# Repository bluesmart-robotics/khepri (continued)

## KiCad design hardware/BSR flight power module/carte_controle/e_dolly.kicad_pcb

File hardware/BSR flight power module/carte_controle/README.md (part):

# Carte de contrôle — BSR flight power module (KHEPRI)

Carte « cerveau » de l'instrument de tableau de bord KHEPRI (motorisation,
IHM, variomètre, alimentation de secours). Elle est empilée sur la
**BSR Drive 3.7**, la carte de puissance qui pilote les deux moteurs.

Projet KiCad 9 (`e_dolly.kicad_pro`, nom hérité de la carte E-dolly dont elle
dérive), 4 couches, **80 × 150 mm**.

> Cette copie a volontairement divergé de la carte de contrôle du dépôt
> E-dolly, qui garde son E-stop et ses contacteurs. Ne pas reporter les
> changements dans E-dolly.

---

## 1. Vue d'ensemble

```
                XT60 2+4 J17 vers la BSR Drive (bus pack 42-51 V)
                                   │
          ┌────────────────────────┴───────────────────────────┐
          │  TVS U8 ─ U2 TPS54560 ─► +24V ─┬─► ventilateur J25  │
          │                                ├─► chargeur secours │
          │                                └─► diode idéale ─┐  │
          │   cellules 2S J21+J22 ─► Q14 ─► diode idéale ────┤  │
          │                                       VSYS_OR ─ R70 ─► +VSYS
          │      +VSYS ─┬─► U1 MP2565 ─► +3.3V (ESP32, logique) │
          │             ├─► U20 L78L05 ─► +5V_SENS ─► 3 LDO capteurs
          │             └─► U30 AP63205 ─► +5V_IHM ─► façade (J20)
          │                                                     │
          │  +36V ─ U43 LM5146 ─► +24V_EXT 10 A ─► J26 faisceau     │
          │  ESP32 U6 ── CAN (U3) ── J28 (BSR Drive) / J26 (faisceau)
          │      ├── I²C ─ TCA9548A U5 ─ ch0 PMP / ch1 secours /  │
          │      │            ch2 pression / ch3 env. / ch4 PCA9555│
          │      ├── SPI ─ IMU U4                                  │
          │      ├── UART1/UART2 ─ façade (J20)                    │
          │      └── PWM/tachy ─ ventilateur (J25)                 │
          └─────────────────────────────────────────────────────┘
```

L'ESP32 de cette carte est la **référence unique** : il est le seul à envoyer
les consignes à la BSR Drive (CAN). La façade (smart knob, écrans) ne fait que
proposer des consignes, que l'ESP32 valide.

### Feuilles du schéma

| Feuille | Contenu |
|---|---|
| `e_dolly.kicad_sch` (racine) | ESP32, CAN, IMU, multiplexeur I²C, USB, alimentations 24 V et 3,3 V, mesure de tension bus |
| `capteurs_pression.kicad_sch` | variomètre et anémomètre : 2 × MS5611 + HSC, leurs alimentations |
| `liaison_ihm.kicad_sch` | nappe vers la carte façade, alimentation 5V_IHM |
| `alim_secours.kicad_sch` | batterie de secours 2S, chargeur, jauge, OU par diodes idéales |
| `mesures_env.kicad_sch` | température d'air, courant et tension consommés par l'instrument |
| `interface_pmp.kicad_sch` | liaison vers la carte de charge USB-C EPR (PMP41115) |
| `ventilation.kicad_sch` | commande du ventilateur de la BSR Drive |
| `faisceau_au.kicad_sch` | XT60 J17, trous de fixation, liaison BSR Drive, faisceau chaussettes 24 V, arrêt d'urgence, expandeur I²C |

---

## 2. Alimentations

| Rail | Produit par | Depuis | Alimente |
|---|---|---|---|
| **+36V** (nom historique) | — | bus du pack 42–51 V via la XT60 J17 | U2, U43, mesure bus (R41–R43), TVS U8 SMCJ58A, C24 100 µF |
| **+24V_EXT** (≈ 24,3 V, 10 A) | U43 LM5146 + Q18/Q19 NTMFS6H800NL, L16 10 µH XAL1510 | +36V | faisceau des chaussettes (J26), coupable |
| **+24V** (≈ 25 V) | U2 TPS54560, L2 15,4 µH, D2 | +36V | diode idéale bus (U36/Q12), 5V_CHG (U34), ventilateur J25 |
| **VSYS_OR** | OU de U36/Q12 (bus) et U37/Q13 (secours) | +24V ou cellules 2S | shunt R70 |
| **+VSYS** | R70 20 mΩ | VSYS_OR | U1, U20, U30. Vaut ≈ 25 V sur bus, 6–8,4 V sur secours |
| **+3.3V** | U1 MP2565, L1 10 µH | +VSYS | ESP32, CAN, IMU, TCA9548A, CP2102N, I²C |
| **+5V_SENS** | U20 L78L05 (100 mA) | +VSYS | 3 LDO LP5907 des capteurs de pression |
| **+3V3_STAT / _TE / _PITOT** | U21 / U22 / U23 LP5907, ferrites L10–L12 | +5V_SENS | un capteur de pression chacun |
| **+5V_IHM** (2 A) | U30 AP63205, L13 6,8 µH | +VSYS | carte façade (J20), coupable par IO13 |
| **+5V_CHG** | U34 AP63205, L14 6,8 µH | +24V (bus seul) | chargeur BQ25887 |
| **BAT_P** (6–8,4 V) | cellules 2S J21 + J22 via F1 | — | chargeur, jauge, Q14 |

Points à comprendre :
- **Sans bus** (planeur éteint, BMS ouvert), +24V tombe. Si l'interrupteur
  J23 est fermé, la batterie de secours alimente +VSYS via U37/Q13 :
  l'instrument démarre, affiche, logue et peut envoyer l'ordre CAN d'armement
  au BMS. Quand le bus arrive, +24V (25 V) dépasse la batterie (≤ 8,4 V) et
  la diode idéale côté secours se bloque toute seule.
- **Tout ce qui est en aval de +VSYS doit accepter 6 V** : U1 (VIN ≥ 4,5 V),
  U30 (VIN ≥ 3,8 V, sortie 5 V un peu juste à 6 V), U20 L78L05 (sortie ≈ 4,3 V
  à 6 V d'entrée, suffisant pour les LDO 3,3 V).
- Le chargeur n'est alimenté que par le bus (U34 sur +24V) : il ne peut pas
  « se charger lui-même » en boucle sur la batterie.

Valeurs à recontrôler : U2 sortie = 0,8 V × (1 + R21/R22) = 0,8 × (1 + 100k/3,3k)
≈ 25 V ; U1 sortie = 0,8 V × (1 + R18/R14) = 0,8 × (1 + 127k/40,2k) ≈ 3,33 V.

---

## 3. Calculateur et communications

### ESP32-WROOM-32UE (U6) — affectation de toutes les broches

| GPIO | Broche | Fonction | Réseau | Vers |
|---|---|---|---|---|
| EN | 3 | reset | /EN | SW1, R25/C17 |
| IO0 | 25 | boot | /IO0 | SW2, R27 |
| IO1 / IO3 | 35 / 34 | UART0 programmation et console | ESP_TX / ESP_RX | CP2102N U7, LED D4/D3 |
| IO16 / IO17 | 27 / 28 | CAN RX / TX | /RXD, /TXD | SN65HVD230 U3 |
| IO5 / IO4 | 29 / 26 | I²C principal SDA / SCL (pull-up R23/R20) | /SDA, /SCL | TCA9548A U5 |
| IO22 / IO23 / IO25 | 36 / 37 / 10 | SPI SCLK / MOSI / MISO | /SCLK /MOSI /MISO | IMU U4 |
| IO26 | 11 | SPI CS IMU (pull-up R17) | /IO26 | U4 |
| IO27 | 12 | interruption IMU | /IO27 | U4 INT1 |
| IO33 | 9 | ADC tension bus | /PDT_pwr_switched | pont R41+R42 / R43, R44, C25, clamp D7 |
| IO18 / IO34 | 30 / 6 | UART1 TX / RX ↔ STM32 haptique | IHM_TX1 / IHM_RX1 | J20 |
| IO19 / IO35 | 31 / 7 | UART2 TX / RX ↔ ESP32-S3 façade | IHM_TX2 / IHM_RX2 | J20 |
| IO21 | 33 | NRST du STM32 (drain ouvert) | IHM_NRST | J20 |
| IO14 | 13 | BOOT0 du STM32 | IHM_BOOT0 | J20 |
| IO13 | 16 | coupure 5V_IHM (haut = coupé) | IHM_PWR_OFF | Q10 |
| IO36 (SENSOR_VP) | 4 | interruption commune (entrée seule) | INT_PWR | PMP, BQ25887, MAX17205, TMP117, INA226 |
| IO12 | 14 | autorisation de charge PMP (pull-down R84, **doit rester bas au boot**) | PMP_CHG_EN | J24 |
| IO15 | 23 | PWM ventilateur | FAN_PWM | Q15 |
| IO39 (SENSOR_VN) | 5 | tachymètre ventilateur (entrée seule) | FAN_TACH | J25 |

**Plus aucune broche libre.** Les commandes ajoutées ensuite (faisceau,
arrêt d'urgence) passent par l'expandeur PCA9555 (§ 9).

### CAN — U3 SN65HVD230

- Relié à la BSR Drive par J28 et au faisceau des chaussettes par J26 (§ 9).
  L'ancienne XT60 J17 et l'ancien connecteur J4 sont supprimés.
- Terminaison 120 Ω (R112) **commutable** par le cavalier JP1 « TERM CAN ».
  L'ancienne terminaison fixe R19 est supprimée.
- R15 10 k sur Rs : mode pente contrôlée.

### I²C — multiplexeur TCA9548A (U5, 0x70)

| Canal | Réseau | Composants (adresse) | Pull-up |
|---|---|---|---|
| 0 | I2C_PMP | carte de charge PMP41115 via J24 | R82/R83 4,7 k |
| 1 | I2C_PWR | BQ25887 (0x6B), MAX17205 (0x36 et 0x0B) | R99/R100 4,7 k |
| 2 | I2C_PRES | MS5611 statique (0x76), MS5611 TE (0x77), HSC (0x28) | R50/R51 4,7 k (sur +3V3_STAT) |
| 3 | I2C_ENV | TMP117 (0x48), INA226 (0x40) | R80/R81 4,7 k |
| 4 | I2C_X | PCA9555 (0x20) | R107/R108 4,7 k |
| 5–7 | — | libres | — |

### Autres

- **IMU U4 ICM-42688-P** (accéléromètre et gyroscope 6 axes, SPI) : fusion
  avec les capteurs de pression pour le vario.
- **USB U7 CP2102N** : programmation de l'ESP32 par J14 (JST PH 6 vers une
  prise USB-C déportée), LED TX/RX D3/D4, reset automatique.
- **SW1** = EN (reset), **SW2** = IO0 (boot).

---

## 4. Variomètre et anémomètre (`capteurs_pression.kicad_sch`, haut de carte)

| Capteur | Réf. | Mesure | Repère sérigraphie |
|---|---|---|---|
| MS5611 | U24 | pression statique (altitude, vario brut) | `P-statique` |
| MS5611 | U25 | pression de la sonde d'énergie totale (vario compensé) | `P-TE` |
| HSCMRRN001PD2A3 | U26 | Δp pitot ±1 psi (vitesse air) | `Δp pitot`, ports `P-tot` / `P-stat` |

- Chaque capteur a sa propre chaîne d'alimentation : ferrite, LDO LP5907
  3,3 V faible bruit et découplage, pour que le bruit numérique ne pollue pas
  la mesure.
- Les deux MS5611 sont chacun dans une **zone de capot étanche** de
  11 × 12 mm (`CAPOT_STATIQUE`, `CAPOT_TE`) : contour en sérigraphie et zone
  d'interdiction de vias, car un via sous le capot ferait fuir l'air. Les capots
  sont imprimés en 3D et reliés aux prises par tube.
- Le HSC a ses propres embouts cannelés ; ses ports sortent vers le bord haut.

---

## 5. Liaison façade (`liaison_ihm.kicad_sch`, bord droit)

Une seule nappe **J20 JST-GH 12 voies** vers la carte façade (smart knob
STM32 + écran 1,64" ESP32-S3 fusionnés ; l'écran 1,75" est raccordé à la
façade). Tout est en 3,3 V.

| J20 | Signal | ESP32 |
|---|---|---|
| 1, 2, 3 | +5V_IHM (2 A au total) | — |
| 4, 11, 12 | GND | — |
| 5 | TX1 → RX du STM32 | IO18 |
| 6 | RX1 ← TX du STM32 | IO34 |
| 7 | TX2 → RX de l'ESP32-S3 | IO19 |
| 8 | RX2 ← TX de l'ESP32-S3 | IO35 |
| 9 | NRST du STM32 | IO21 |
| 10 | BOOT0 du STM32 | IO14 |

- **Côté façade, croiser TX et RX.** Prendre l'USART1 du STM32 (PA9/PA10)
  pour que le reflash par BOOT0 fonctionne.
- Protections : 100 Ω en série sur chaque ligne (R54–R59), pull-up 10 k sur
  les deux RX (R60/R61, IO34/35 n'en ont pas), pull-down 10 k sur BOOT0
  (R62), diodes ESD TPD4E05U06 (U31, U32).
- Alimentation : U30 AP63205. Son EN est tiré à +VSYS (R52) ; Q10 le met à la
  masse quand IO13 est haut. La façade est donc alimentée par défaut, et
  l'ESP32 peut la redémarrer à froid.

---

## 6. Alimentation de secours (`alim_secours.kicad_sch`, bande gauche)

- **Deux cellules Li-ion 18650 en série (2S)**. J21 à gauche = cellule basse,
  J22 à droite = cellule haute, JST PH 2.0 2 voies, **1 = −, 2 = +** sur les
  deux. Le point milieu BAT_MID relie le + de J21 au − de J22.
  **Cellules protégées (PCM intégré) obligatoires.**
  Pourquoi la série : à 6–8,4 V, la batterie se met en OU directement sur
  +VSYS, sans convertisseur élévateur.
- **F1** fusible réarmable 1812 sur le + de la pile, **R71** 10 mΩ côté −
  (shunt de la jauge).
- **J23 interrupteur de tableau de bord** (PH 2.0 2P) : contact fermé entre
  les broches 1 et 2 → Q14 (PMOS AO3401A) conduit et branche la batterie.
  Ouvert, la batterie est isolée : elle ne se vide pas au parking. Une diode
  idéale seule ne suffirait pas, la diode interne du MOSFET conduirait.
- **OU par diodes idéales** : U36 LM74700 + Q12 SI2318 côté bus (+24V),
  U37 + Q13 côté secours (BAT_SW). Sortie commune VSYS_OR → R70 → +VSYS.
- **Chargeur U35 BQ25887** (élévateur 2S, équilibrage des cellules, I²C 0x6B) :
  - entrée +5V_CHG (U34, depuis le bus seulement) ;
  - courant d'entrée limité à 1 A max par R88 1,27 kΩ, réglable plus bas en I²C ;
  - équilibrage par R91 100 Ω (≈ 40 mA), R92 300 Ω de protection sur MID ;
  - thermistance TH1 (pont R89/R90) ;
  - CD et PSEL à la masse (charge autorisée, mode adaptateur) ;
  - ~INT sur INT_PWR ; ~PG et ~STAT non utilisés.
- **Jauge U38 MAX17205** (ModelGauge m5) : état de charge, tension de chaque
  cellule, courant via R71 ; I²C 0x36 / 0x0B ; alerte sur INT_PWR ;
  thermistance TH2 sur AIN1.

---

## 7. Mesures d'environnement et carte de charge

**`mesures_env.kicad_sch`** (en haut à gauche, à côté des capteurs de
pression) :
- **U40 TMP117** (0x48, ±0,1 °C) : température de l'air, pour la vitesse
  vraie et la densité. À garder loin des sources de chaleur.
- **U41 INA226** (0x40) : courant et tension de +VSYS, c'est-à-dire la
  consommation totale de l'instrument, sur bus comme sur secours. Shunt R70
  20 mΩ, filtre R96/R97/C62.

**`interface_pmp.kicad_sch`** — J24 JST PH 2.0 6 voies, sérigraphie
« to USB-C EPR », vers la carte de charge PMP41115 empilée :

| J24 | Signal |
|---|---|
| 1 | GND |
| 2 | +3,3 V (référence logique et pull-up) |
| 3 / 4 | SDA / SCL (canal 0) |
| 5 | INT (ligne commune INT_PWR, drain ouvert, pull-up R85) |
| 6 | CHG_EN (IO12, pull-down R84) |

La puissance de charge (240 W) ne passe pas par ce connecteur : elle va directement
sur le bus du pack.

---

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
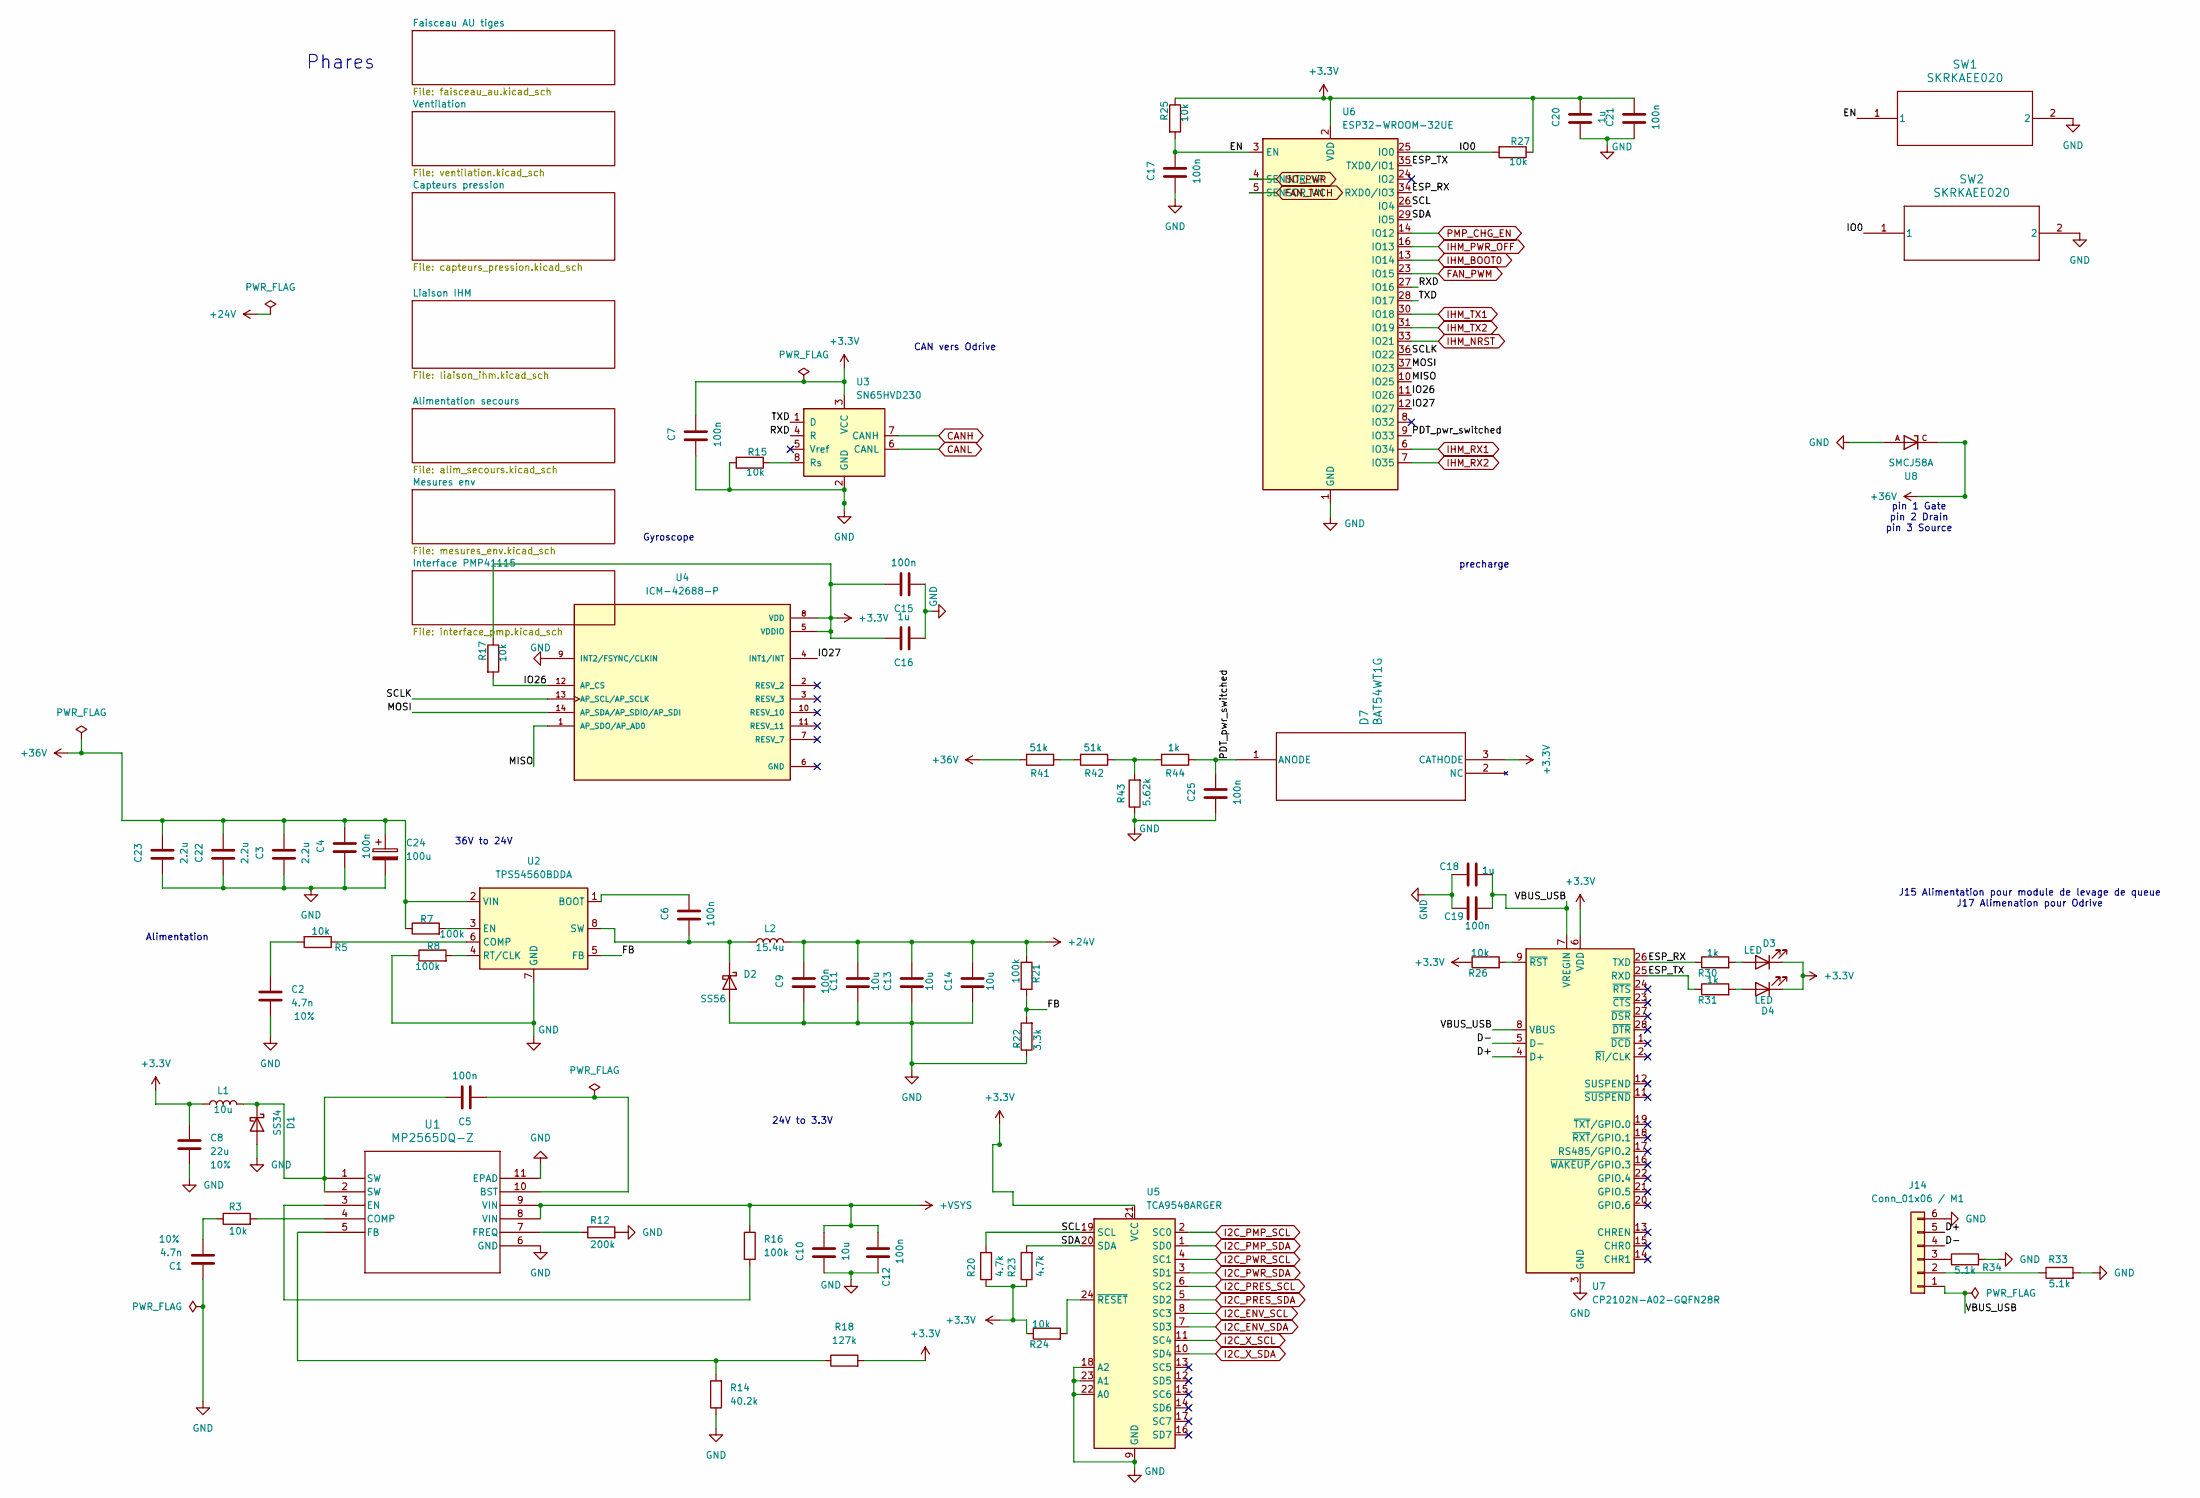
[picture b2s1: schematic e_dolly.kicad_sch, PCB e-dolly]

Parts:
C1, C2: 4.7n; C_0603_1608Metric; tolerance 10%; MPN CL10B472KB8NNNC; LCSC C1621
C3, C22, C23: 2.2u; C_1210_3225Metric; MPN GRM32ER72A225KA35L; LCSC C86054
C4: 100n; C_0805_2012Metric; MPN GCM21BR72A104KA37L; LCSC C85866
C5, C6, C7, C9, C12, C15, C17, C19, C21, C25: 100n; C_0603_1608Metric; MPN CL10B104KB8NNNC; LCSC C1591
C8: 22u; C_1206_3216Metric; tolerance 10%; MPN CL31A226KQHNNNE; LCSC C159759
C10: 10u; C_0805_2012Metric; MPN CL21A106KOQNNNE; LCSC C1713
C11, C13, C14: 10u; C_1210_3225Metric; MPN GRM32ER71H106KA12L; LCSC C77102
C16, C18, C20: 1u; C_0603_1608Metric; MPN CL10A105KB8NNNC; LCSC C15849
C24: 100u; CP_Elec_10x10.5; MPN EEEFN1J101P; LCSC C494866
D1: SS34; D_SMB; MPN DSS34; LCSC C41369490
D2: SS56; D_SMA; MPN SS56; LCSC C65009
D3, D4: LED; D_SOD-323; MPN LTST-C235KGKRKT; LCSC C125110
D7: BAT54WT1G; SOT-323-3_2P2X1P35_ONS
J14: Conn_01x06 / M1; JST_PH_B6B-PH-K_1x06_P2.00mm_Vertical; MPN B6B-PH-K-S(LF)(SN); LCSC C131342
L1: 10u; L_7.1x6.6mm; MPN SMMS0650-100M; LCSC C149584
L2: 15.4u; L_7.1x6.6mm; MPN SMMS0650-150M; LCSC C149585
R3: 10k; R_0603_1608Metric; MPN RT0603BRD0710KL; LCSC C95204
R5, R15, R17, R24, R25, R26, R27: 10k; R_0402_1005Metric; MPN RC0402FR-0710KL; LCSC C60490
R7, R8, R16, R21: 100k; R_0603_1608Metric; MPN RC0603FR-07100KL; LCSC C14675
R12: 200k; R_0603_1608Metric; MPN RC0603FR-07200KL; LCSC C105574
R14: 40.2k; R_0603_1608Metric; MPN RC0603FR-0740K2L; LCSC C137723
R18: 127k; R_0603_1608Metric; MPN RT0603FRE07127KL; LCSC C706120
R20, R23: 4.7k; R_0603_1608Metric; MPN RC0603FR-074K7L; LCSC C99782
R22: 3.3k; R_0402_1005Metric; MPN RC0603FR-073K3L; LCSC C108078
R30, R31, R44: 1k; R_0603_1608Metric; MPN RC0603FR-071KL; LCSC C22548
R33, R34: 5.1k; R_0603_1608Metric; MPN RC0603FR-075K1L; LCSC C105580
R41, R42: 51k; R_0805_2012Metric; MPN RC0805FR-0751KL; LCSC C107233
R43: 5.62k; R_0603_1608Metric; MPN RC0603FR-075K62L; LCSC C183220
SW1, SW2: SKRKAEE020; SW2_SKRKAEE020_ALPS; MPN SKRKAEE020; LCSC C115357
U1: MP2565DQ-Z; QFN10_MP2565_MNP; MPN MP2459GJ-Z-MS; LCSC C45367195
U2: TPS54560BDDA; Texas_R-PDSO-G8_EP2.95x4.9mm_Mask2.4x3.1mm_ThermalVias; MPN TPS54560DDA; LCSC C465738
U3: SN65HVD230; SOIC-8_3.9x4.9mm_P1.27mm; MPN SN65HVD230DR-JSM; LCSC C46596299
U4: ICM-42688-P; PQFN50P300X250X97-14N; PARTREV 1.2; LCSC C1850418
U5: TCA9548ARGER; Texas_RGE0024C_VQFN-24-1EP_4x4mm_P0.5mm_EP2.1x2.1mm; MPN TCA9548ARGER; LCSC C555456
U6: ESP32-WROOM-32UE; MPN ESP32-WROOM-32UE-N16; LCSC C701346
U7: CP2102N-A02-GQFN28R; QFN-28-1EP_5x5mm_P0.5mm_EP3.35x3.35mm; MPN CP2102N-A02-GQFN28R; LCSC C964632
U8: SMCJ58A; DIOM6859X262N; PARTREV R2102; LCSC C3720689

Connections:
+3.3V: C7.2, C8.1, C15.2, C16.2, C20.2, C21.2, D3.1 (K), D4.1 (K), D7.3 (CATHODE), L1.1, R17.1, R18.2, R20.1, R23.1, R24.1, R25.1, R26.1, R27.1, U3.3 (VCC), U4.5 (VDDIO), U4.8 (VDD), U5.21 (VCC), U6.2 (VDD), U7.6 (VDD); also elsewhere on the board
+24V: C9.2, C11.2, C13.2, C14.2, L2.2, R21.1; also elsewhere on the board
+36V: C3.2, C4.2, C22.2, C23.2, C24.1, R7.1, R41.2, U2.2 (VIN), U8.C; also elsewhere on the board
+VSYS: C10.2, C12.2, R16.1, U1.8 (VIN), U1.9 (VIN); also elsewhere on the board
/D+: J14.5, U7.4 (D+)
/D-: J14.4, U7.5 (D-)
/EN: C17.2, R25.2, SW1.1, U6.3 (EN)
/ESP_RX: R30.1, U6.34 (RXD0/IO3), U7.26 (TXD)
/ESP_TX: R31.1, U6.35 (TXD0/IO1), U7.25 (RXD)
/FB: R21.2, R22.2, U2.5 (FB)
/IO0: R27.2, SW2.1, U6.25 (IO0)
/IO26: R17.2, U4.12 (AP_CS), U6.11 (IO26)
/IO27: U4.4 (INT1/INT), U6.12 (IO27)
/MISO: U4.1 (AP_SDO/AP_AD0), U6.10 (IO25)
/MOSI: U4.14 (AP_SDA/AP_SDIO/AP_SDI), U6.37 (IO23)
/PDT_pwr_switched: C25.2, D7.1 (ANODE), R44.1, U6.9 (IO33)
/RXD: U3.4 (R), U6.27 (IO16)
/SCL: R20.2, U5.19 (SCL), U6.26 (IO4)
/SCLK: U4.13 (AP_SCL/AP_SCLK), U6.36 (IO22)
/SDA: R23.2, U5.20 (SDA), U6.29 (IO5)
/TXD: U3.1 (D), U6.28 (IO17)
/VBUS_USB: C18.2, C19.2, J14.1, U7.7 (VREGIN), U7.8 (VBUS)
CANH: U3.7 (CANH); also elsewhere on the board
CANL: U3.6 (CANL); also elsewhere on the board
FAN_PWM: U6.23 (IO15); also elsewhere on the board
FAN_TACH: U6.5 (SENSOR_VN); also elsewhere on the board
GND: C1.1, C2.2, C3.1, C4.1, C7.1, C8.2, C9.1, C10.1, C11.1, C12.1, C13.1, C14.1, C15.1, C16.1, C17.1, C18.1, C19.1, C20.1, C21.1, C22.1, C23.1, C24.2, C25.1, D1.2 (A), D2.2 (A), J14.6, R8.1, R12.2, R14.1, R15.2, R22.1, R33.2, R34.2, R43.1, SW1.2, SW2.2, U1.6 (GND), U1.11 (EPAD), U2.7 (GND), U2.9 (GND), U3.2 (GND), U4.9 (INT2/FSYNC/CLKIN), U5.9 (GND), U5.18 (A2), U5.22 (A0), U5.23 (A1), U6.1 (GND), U6.15 (GND), U6.38 (GND), U6.39 (GND), U7.3 (GND), U7.29 (GND), U8.A; also elsewhere on the board
I2C_ENV_SCL: U5.8 (SC3); also elsewhere on the board
I2C_ENV_SDA: U5.7 (SD3); also elsewhere on the board
I2C_PMP_SCL: U5.2 (SC0); also elsewhere on the board
I2C_PMP_SDA: U5.1 (SD0); also elsewhere on the board
I2C_PRES_SCL: U5.6 (SC2); also elsewhere on the board
I2C_PRES_SDA: U5.5 (SD2); also elsewhere on the board
I2C_PWR_SCL: U5.4 (SC1); also elsewhere on the board
I2C_PWR_SDA: U5.3 (SD1); also elsewhere on the board
I2C_X_SCL: U5.11 (SC4); also elsewhere on the board
I2C_X_SDA: U5.10 (SD4); also elsewhere on the board
IHM_BOOT0: U6.13 (IO14); also elsewhere on the board
IHM_NRST: U6.33 (IO21); also elsewhere on the board
IHM_PWR_OFF: U6.16 (IO13); also elsewhere on the board
IHM_RX1: U6.6 (IO34); also elsewhere on the board
IHM_RX2: U6.7 (IO35); also elsewhere on the board
IHM_TX1: U6.30 (IO18); also elsewhere on the board
IHM_TX2: U6.31 (IO19); also elsewhere on the board
INT_PWR: U6.4 (SENSOR_VP); also elsewhere on the board
unnamed: C1.2, R3.1
unnamed: C2.1, R5.2
unnamed: C5.2, D1.1 (K), L1.2, U1.1 (SW), U1.2 (SW)
unnamed: C6.1, D2.1 (K), L2.1, U2.8 (SW)
unnamed: D3.2 (A), R30.2
unnamed: D4.2 (A), R31.2
unnamed: J14.2, R33.1
unnamed: J14.3, R34.1
unnamed: R41.1, R42.2
unnamed: R42.1, R43.2, R44.2
unnamed: C5.1, U1.10 (BST)
unnamed: R3.2, U1.4 (COMP)
unnamed: R16.2, U1.3 (EN)
unnamed: R14.2, R18.1, U1.5 (FB)
unnamed: R12.1, U1.7 (FREQ)
unnamed: C6.2, U2.1 (BOOT)
unnamed: R5.1, U2.6 (COMP)
unnamed: R7.2, U2.3 (EN)
unnamed: R8.2, U2.4 (RT/CLK)
unnamed: R15.1, U3.8 (Rs)
unnamed: R24.2, U5.24 (~RESET)
unnamed: R26.2, U7.9 (~RST)
PMP_CHG_EN: U6.14 (IO12); also elsewhere on the board

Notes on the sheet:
Alimentation
pin 1 Gate pin 2 Drain pin 3 Source
Phares
36V to 24V
Gyroscope
precharge
24V to 3.3V
J15 Alimentation pour module de levage de queue J17 Alimenation pour Odrive
CAN vers Odrive

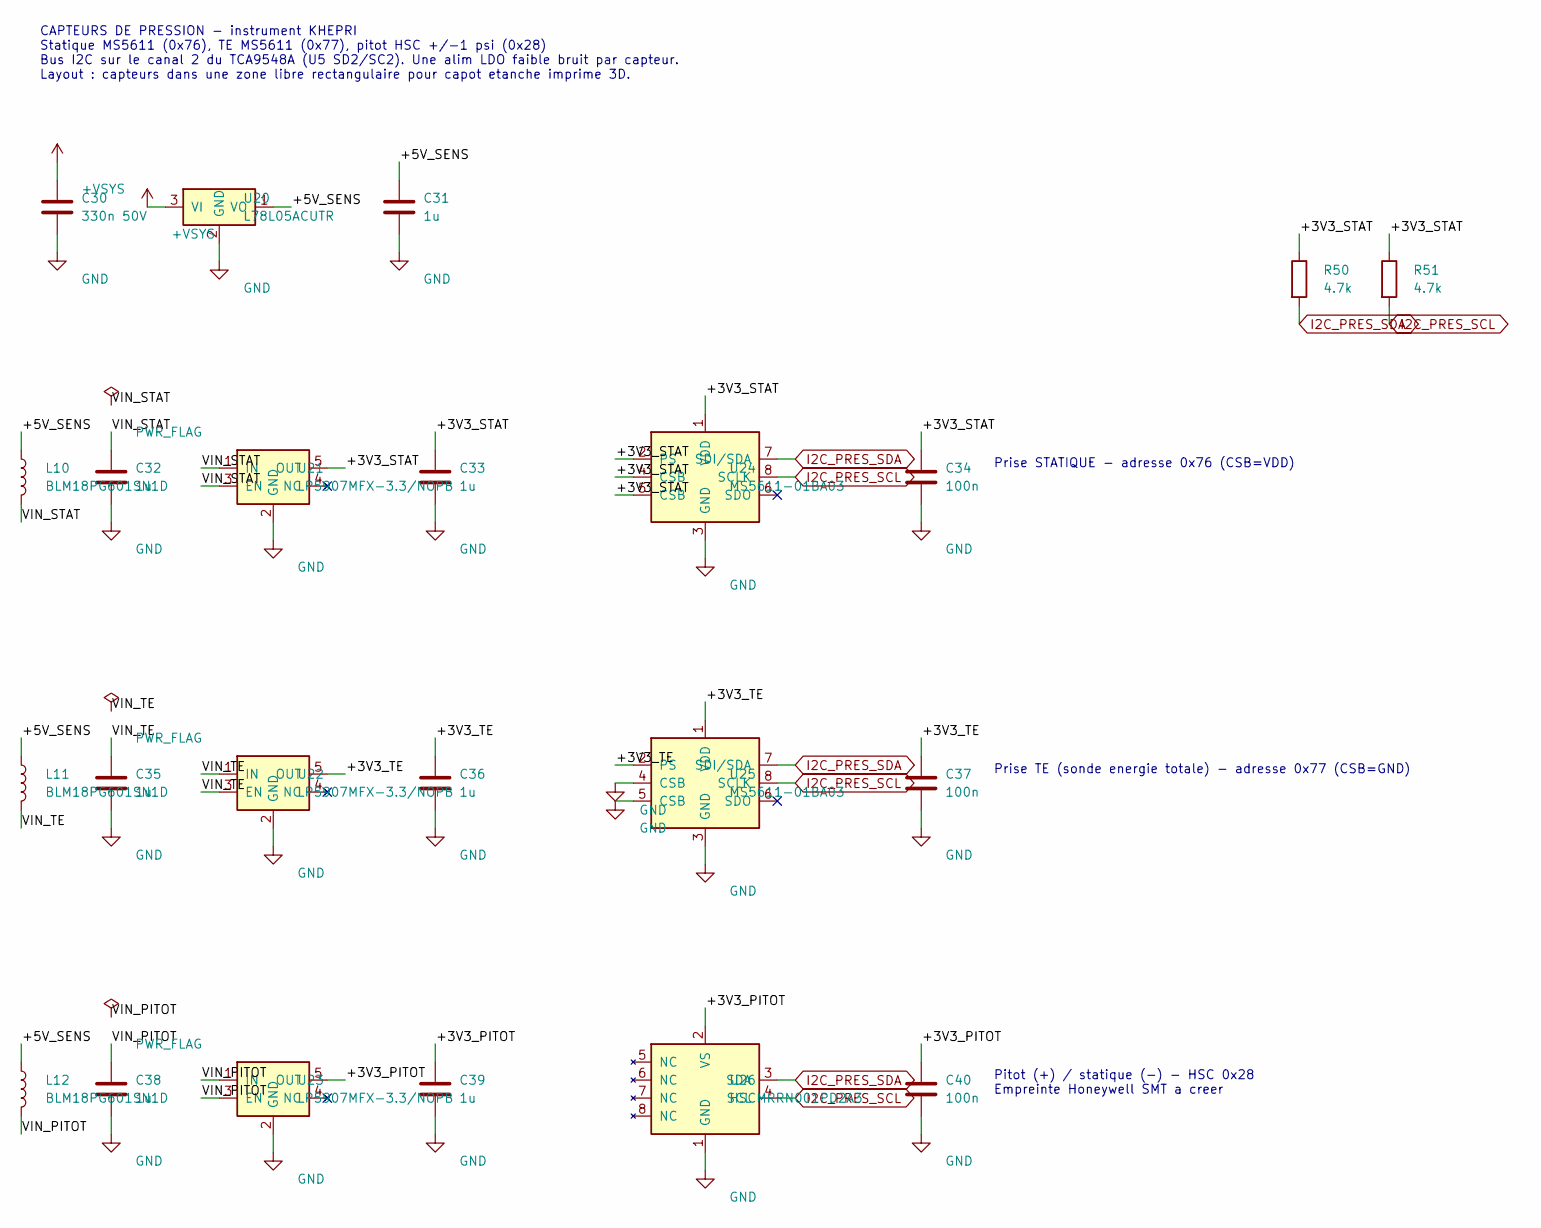
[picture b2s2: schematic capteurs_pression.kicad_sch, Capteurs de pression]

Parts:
C30: 330n 50V; C_0603_1608Metric
C31, C32, C33, C35, C36, C38, C39: 1u; C_0603_1608Metric
C34, C37, C40: 100n; C_0603_1608Metric
L10, L11, L12: BLM18PG601SN1D; L_0603_1608Metric
R50, R51: 4.7k; R_0603_1608Metric
U20: L78L05ACUTR; SOT-89-3
U21, U22, U23: LP5907MFX-3.3/NOPB; SOT-23-5
U24, U25: MS5611-01BA03; LGA-8_3x5mm_P1.25mm
U26: HSCMRRN001PD2A3; Honeywell_HSC_SMT_RR_PROVISOIRE

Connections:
+VSYS: C30.1, U20.3 (VI); also elsewhere on the board
/Capteurs pression/+3V3_PITOT: C39.1, C40.1, U23.5 (OUT), U26.2 (VS)
/Capteurs pression/+3V3_STAT: C33.1, C34.1, R50.1, R51.1, U21.5 (OUT), U24.1 (VDD), U24.2 (PS), U24.4 (CSB), U24.5 (CSB)
/Capteurs pression/+3V3_TE: C36.1, C37.1, U22.5 (OUT), U25.1 (VDD), U25.2 (PS)
/Capteurs pression/+5V_SENS: C31.1, L10.1, L11.1, L12.1, U20.1 (VO)
/Capteurs pression/VIN_PITOT: C38.1, L12.2, U23.1 (IN), U23.3 (EN)
/Capteurs pression/VIN_STAT: C32.1, L10.2, U21.1 (IN), U21.3 (EN)
/Capteurs pression/VIN_TE: C35.1, L11.2, U22.1 (IN), U22.3 (EN)
GND: C30.2, C31.2, C32.2, C33.2, C34.2, C35.2, C36.2, C37.2, C38.2, C39.2, C40.2, U20.2 (GND), U21.2 (GND), U22.2 (GND), U23.2 (GND), U24.3 (GND), U25.3 (GND), U25.4 (CSB), U25.5 (CSB), U26.1 (GND); also elsewhere on the board
I2C_PRES_SCL: R51.2, U24.8 (SCLK), U25.8 (SCLK), U26.4 (SCL); also elsewhere on the board
I2C_PRES_SDA: R50.2, U24.7 (SDI/SDA), U25.7 (SDI/SDA), U26.3 (SDA); also elsewhere on the board

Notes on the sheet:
CAPTEURS DE PRESSION - instrument KHEPRI Statique MS5611 (0x76), TE MS5611 (0x77), pitot HSC +/-1 psi (0x28) Bus I2C sur le canal 2 du TCA9548A (U5 SD2/SC2). Une alim LDO faible bruit par capteur. Layout : capteurs dans une zone libre rectangulaire pour capot etanche imprime 3D.
Prise STATIQUE - adresse 0x76 (CSB=VDD)
Prise TE (sonde energie totale) - adresse 0x77 (CSB=GND)
Pitot (+) / statique (-) - HSC 0x28 Empreinte Honeywell SMT a creer

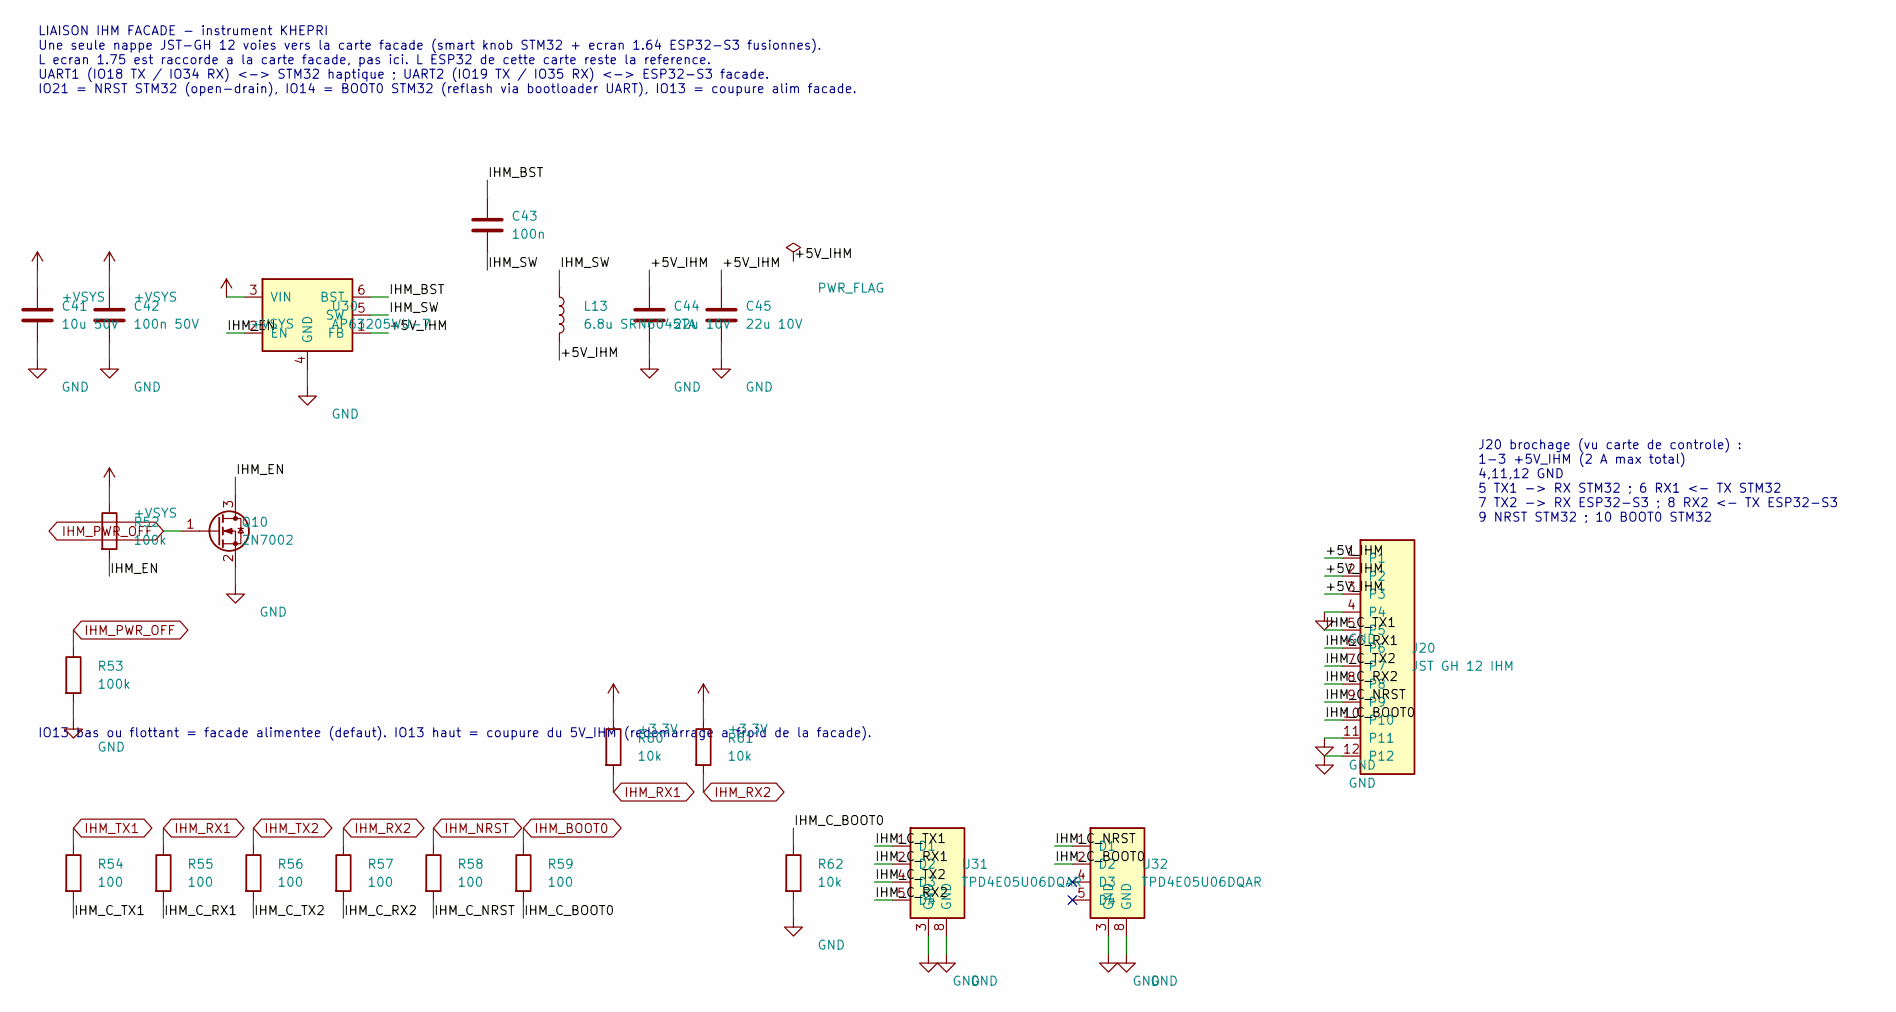
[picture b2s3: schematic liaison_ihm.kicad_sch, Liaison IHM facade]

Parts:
C41: 10u 50V; C_1206_3216Metric
C42: 100n 50V; C_0603_1608Metric
C43: 100n; C_0603_1608Metric
C44, C45: 22u 10V; C_0805_2012Metric
J20: JST GH 12 IHM; JST_GH_BM12B-GHS-TBT_1x12-1MP_P1.25mm_Vertical
L13: 6.8u SRN6045TA; L_Bourns_SRN6045TA
Q10: 2N7002; SOT-23
R52, R53: 100k; R_0603_1608Metric
R54, R55, R56, R57, R58, R59: 100; R_0603_1608Metric
R60, R61, R62: 10k; R_0603_1608Metric
U30: AP63205WU-7; TSOT-23-6
U31, U32: TPD4E05U06DQAR; USON-10_2.5x1.0mm_P0.5mm

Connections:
+3.3V: R60.1, R61.1; also elsewhere on the board
+VSYS: C41.1, C42.1, R52.1, U30.3 (VIN); also elsewhere on the board
/Liaison IHM/+5V_IHM: C44.1, C45.1, J20.1, J20.2, J20.3, L13.2, U30.1 (FB)
/Liaison IHM/IHM_BST: C43.1, U30.6 (BST)
/Liaison IHM/IHM_C_BOOT0: J20.10, R59.2, R62.1, U32.2 (D2)
/Liaison IHM/IHM_C_NRST: J20.9, R58.2, U32.1 (D1)
/Liaison IHM/IHM_C_RX1: J20.6, R55.2, U31.2 (D2)
/Liaison IHM/IHM_C_RX2: J20.8, R57.2, U31.5 (D4)
/Liaison IHM/IHM_C_TX1: J20.5, R54.2, U31.1 (D1)
/Liaison IHM/IHM_C_TX2: J20.7, R56.2, U31.4 (D3)
/Liaison IHM/IHM_EN: Q10.3 (D), R52.2, U30.2 (EN)
/Liaison IHM/IHM_SW: C43.2, L13.1, U30.5 (SW)
GND: C41.2, C42.2, C44.2, C45.2, J20.4, J20.11, J20.12, Q10.2 (S), R53.2, R62.2, U30.4 (GND), U31.3 (GND), U31.8 (GND), U32.3 (GND), U32.8 (GND); also elsewhere on the board
IHM_BOOT0: R59.1; also elsewhere on the board
IHM_NRST: R58.1; also elsewhere on the board
IHM_PWR_OFF: Q10.1 (G), R53.1; also elsewhere on the board
IHM_RX1: R55.1, R60.2; also elsewhere on the board
IHM_RX2: R57.1, R61.2; also elsewhere on the board
IHM_TX1: R54.1; also elsewhere on the board
IHM_TX2: R56.1; also elsewhere on the board

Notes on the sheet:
LIAISON IHM FACADE - instrument KHEPRI Une seule nappe JST-GH 12 voies vers la carte facade (smart knob STM32 + ecran 1.64 ESP32-S3 fusionnes). L ecran 1.75 est raccorde a la carte facade, pas ici. L ESP32 de cette carte reste la reference. UART1 (IO18 TX / IO34 RX) <-> STM32 haptique ; UART2 (IO19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
IO13 bas ou flottant = facade alimentee (defaut). IO13 haut = coupure du 5V_IHM (redemarrage a froid de la facade).
J20 brochage (vu carte de controle) : 1-3 +5V_IHM (2 A max total) 4,11,12 GND 5 TX1 -> RX STM32 ; 6 RX1 <- TX STM32 7 TX2 -> RX ESP32-S3 ; 8 RX2 <- TX ESP32-S3 9 NRST STM32 ; 10 BOOT0 STM32

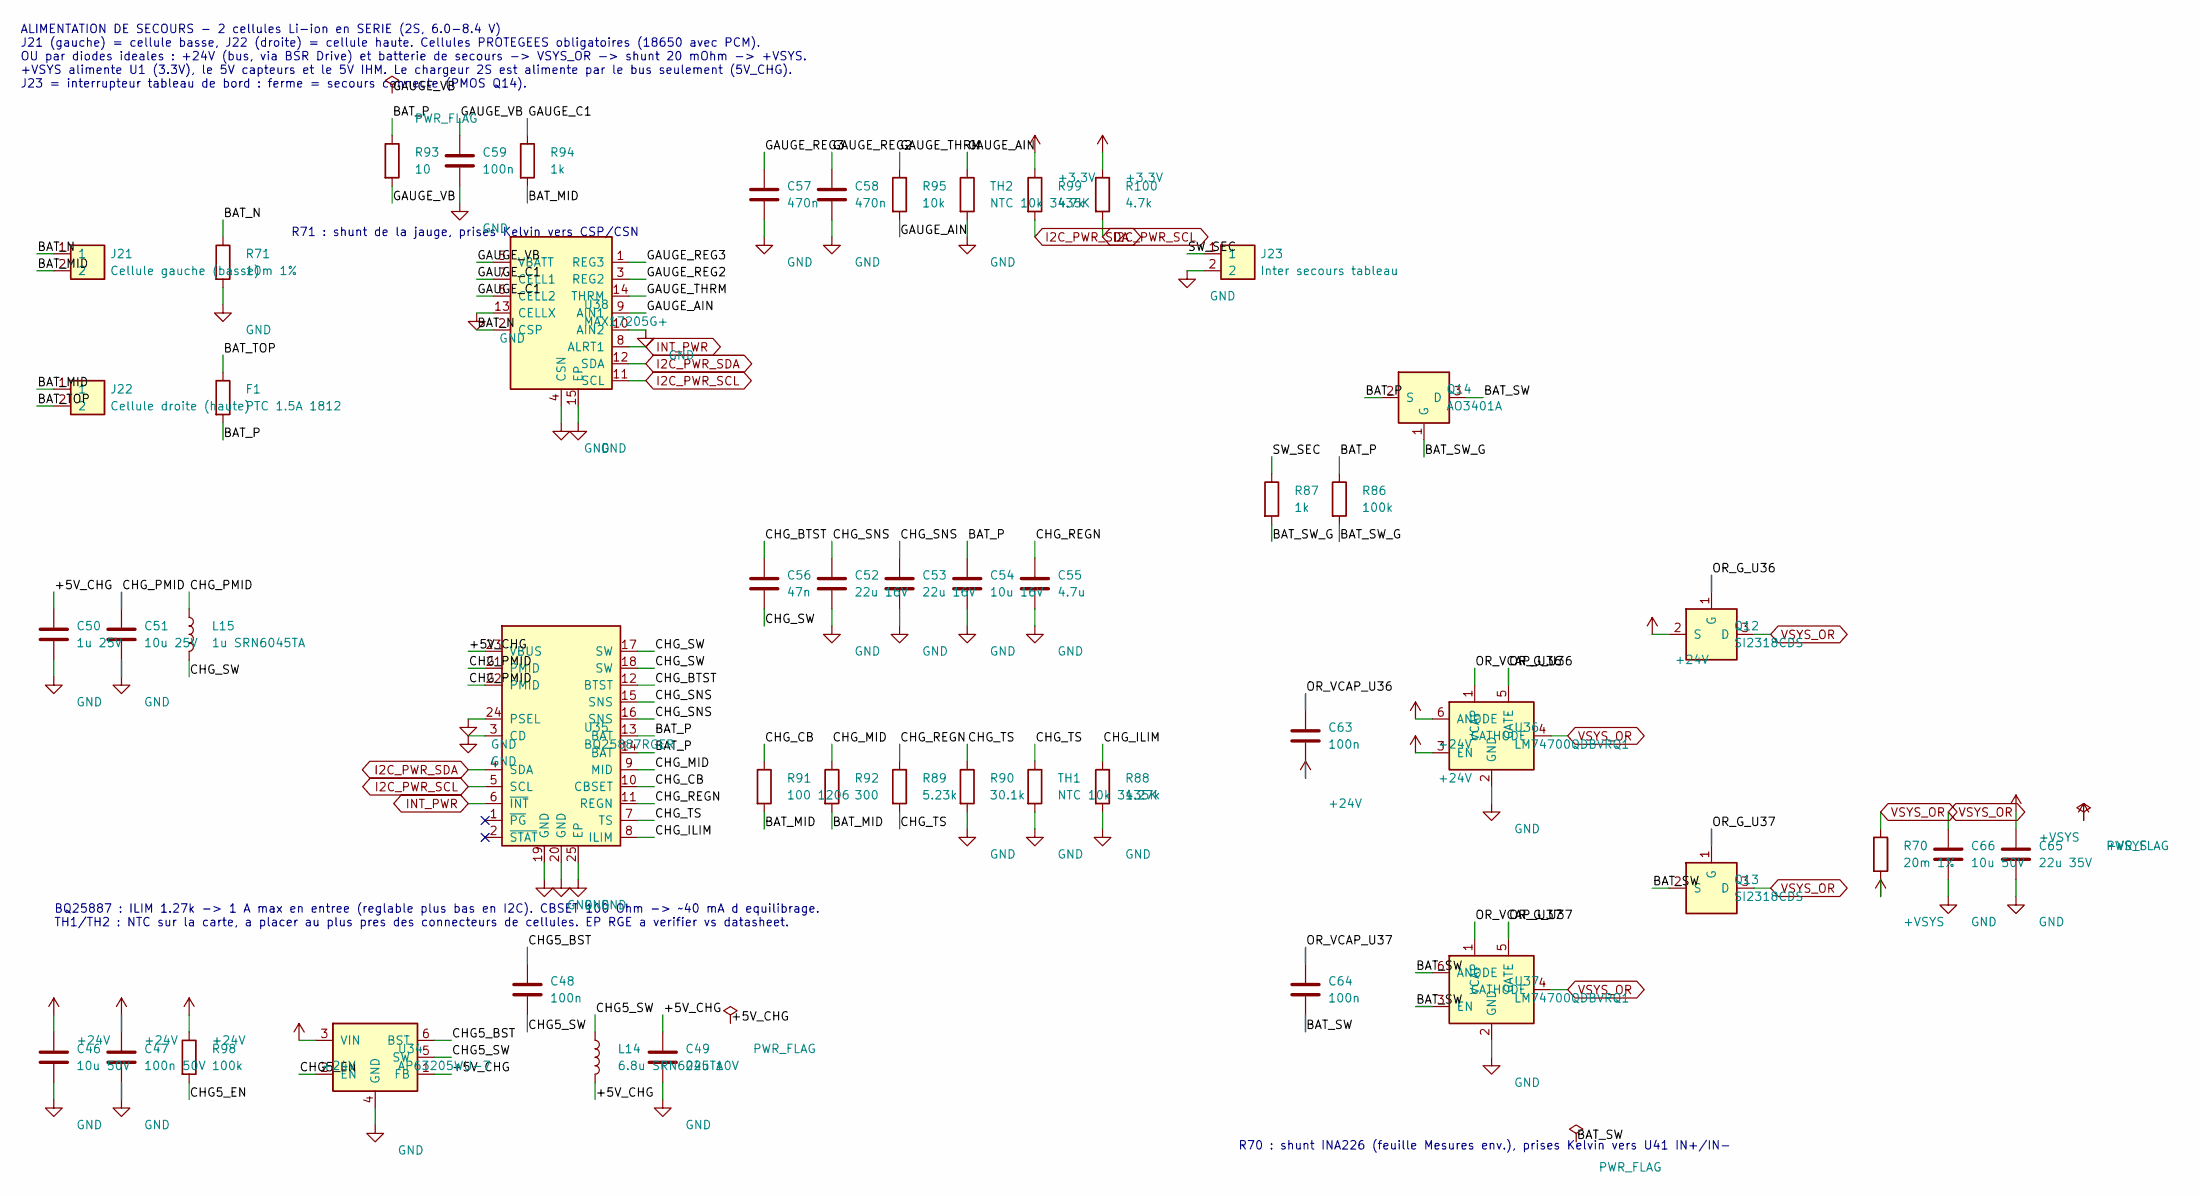
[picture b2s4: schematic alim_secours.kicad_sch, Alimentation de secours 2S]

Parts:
C46, C66: 10u 50V; C_1206_3216Metric
C47: 100n 50V; C_0603_1608Metric
C48, C59, C63, C64: 100n; C_0603_1608Metric
C49: 22u 10V; C_0805_2012Metric
C50: 1u 25V; C_0603_1608Metric
C51: 10u 25V; C_0805_2012Metric
C52, C53: 22u 16V; C_0805_2012Metric
C54: 10u 16V; C_0805_2012Metric
C55: 4.7u; C_0603_1608Metric
C56: 47n; C_0603_1608Metric
C57, C58: 470n; C_0603_1608Metric
C65: 22u 35V; C_1210_3225Metric
F1: PTC 1.5A 1812; Fuse_1812_4532Metric
J21: Cellule gauche (basse); JST_PH_B2B-PH-SM4-TB_1x02-1MP_P2.00mm_Vertical
J22: Cellule droite (haute); JST_PH_B2B-PH-SM4-TB_1x02-1MP_P2.00mm_Vertical
J23: Inter secours tableau; JST_PH_B2B-PH-SM4-TB_1x02-1MP_P2.00mm_Vertical
L14: 6.8u SRN6045TA; L_Bourns_SRN6045TA
L15: 1u SRN6045TA; L_Bourns_SRN6045TA
Q12, Q13: SI2318CDS; SOT-23
Q14: AO3401A; SOT-23
R70: 20m 1%; R_1206_3216Metric
R71: 10m 1%; R_1206_3216Metric
R86, R98: 100k; R_0603_1608Metric
R87, R94: 1k; R_0603_1608Metric
R88: 1.27k; R_0603_1608Metric
R89: 5.23k; R_0603_1608Metric
R90: 30.1k; R_0603_1608Metric
R91: 100 1206; R_1206_3216Metric
R92: 300; R_0603_1608Metric
R93: 10; R_0603_1608Metric
R95: 10k; R_0603_1608Metric
R99, R100: 4.7k; R_0603_1608Metric
TH1, TH2: NTC 10k 3435K; R_0603_1608Metric
U34: AP63205WU-7; TSOT-23-6
U35: BQ25887RGER; Texas_RGE0024C_VQFN-24-1EP_4x4mm_P0.5mm_EP2.1x2.1mm
U36, U37: LM74700QDBVRQ1; SOT-23-6
U38: MAX17205G+; TDFN-14-1EP_3x3mm_P0.4mm_EP1.78x2.35mm

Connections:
+3.3V: R99.1, R100.1; also elsewhere on the board
+24V: C46.1, C47.1, C63.2, Q12.2 (S), R98.1, U34.3 (VIN), U36.3 (EN), U36.6 (ANODE); also elsewhere on the board
+VSYS: C65.1, R70.2; also elsewhere on the board
/Alimentation secours/+5V_CHG: C49.1, C50.1, L14.2, U34.1 (FB), U35.23 (VBUS)
/Alimentation secours/BAT_MID: J21.2, J22.1, R91.2, R92.2, R94.2
/Alimentation secours/BAT_N: J21.1, R71.1, U38.2 (CSP)
/Alimentation secours/BAT_P: C54.1, F1.2, Q14.2 (S), R86.1, R93.1, U35.13 (BAT), U35.14 (BAT)
/Alimentation secours/BAT_SW: C64.2, Q13.2 (S), Q14.3 (D), U37.3 (EN), U37.6 (ANODE)
/Alimentation secours/BAT_SW_G: Q14.1 (G), R86.2, R87.2
/Alimentation secours/BAT_TOP: F1.1, J22.2
/Alimentation secours/CHG5_BST: C48.1, U34.6 (BST)
/Alimentation secours/CHG5_EN: R98.2, U34.2 (EN)
/Alimentation secours/CHG5_SW: C48.2, L14.1, U34.5 (SW)
/Alimentation secours/CHG_BTST: C56.1, U35.12 (BTST)
/Alimentation secours/CHG_CB: R91.1, U35.10 (CBSET)
/Alimentation secours/CHG_ILIM: R88.1, U35.8 (ILIM)
/Alimentation secours/CHG_MID: R92.1, U35.9 (MID)
/Alimentation secours/CHG_PMID: C51.1, L15.1, U35.21 (PMID), U35.22 (PMID)
/Alimentation secours/CHG_REGN: C55.1, R89.1, U35.11 (REGN)
/Alimentation secours/CHG_SNS: C52.1, C53.1, U35.15 (SNS), U35.16 (SNS)
/Alimentation secours/CHG_SW: C56.2, L15.2, U35.17 (SW), U35.18 (SW)
/Alimentation secours/CHG_TS: R89.2, R90.1, TH1.1, U35.7 (TS)
/Alimentation secours/GAUGE_AIN: R95.2, TH2.1, U38.9 (AIN1)
/Alimentation secours/GAUGE_C1: R94.1, U38.6 (CELL2), U38.7 (CELL1)
/Alimentation secours/GAUGE_REG2: C58.1, U38.3 (REG2)
/Alimentation secours/GAUGE_REG3: C57.1, U38.1 (REG3)
/Alimentation secours/GAUGE_THRM: R95.1, U38.14 (THRM)
/Alimentation secours/GAUGE_VB: C59.1, R93.2, U38.5 (VBATT)
/Alimentation secours/OR_G_U36: Q12.1 (G), U36.5 (GATE)
/Alimentation secours/OR_G_U37: Q13.1 (G), U37.5 (GATE)
/Alimentation secours/OR_VCAP_U36: C63.1, U36.1 (VCAP)
/Alimentation secours/OR_VCAP_U37: C64.1, U37.1 (VCAP)
/Alimentation secours/SW_SEC: J23.1, R87.1
GND: C46.2, C47.2, C49.2, C50.2, C51.2, C52.2, C53.2, C54.2, C55.2, C57.2, C58.2, C59.2, C65.2, C66.2, J23.2, R71.2, R88.2, R90.2, TH1.2, TH2.2, U34.4 (GND), U35.3 (CD), U35.19 (GND), U35.20 (GND), U35.24 (PSEL), U35.25 (EP), U36.2 (GND), U37.2 (GND), U38.4 (CSN), U38.10 (AIN2), U38.13 (CELLX), U38.15 (EP); also elsewhere on the board
I2C_PWR_SCL: R100.2, U35.5 (SCL), U38.11 (SCL); also elsewhere on the board
I2C_PWR_SDA: R99.2, U35.4 (SDA), U38.12 (SDA); also elsewhere on the board
INT_PWR: U35.6 (~INT), U38.8 (ALRT1); also elsewhere on the board
VSYS_OR: C66.1, Q12.3 (D), Q13.3 (D), R70.1, U36.4 (CATHODE), U37.4 (CATHODE); also elsewhere on the board

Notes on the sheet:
ALIMENTATION DE SECOURS - 2 cellules Li-ion en SERIE (2S, 6.0-8.4 V) J21 (gauche) = cellule basse, J22 (droite) = cellule haute. Cellules PROTEGEES obligatoires (18650 avec PCM). OU par diodes ideales : +24V (bus, via BSR Drive) et batterie de secours -> VSYS_OR -> shunt 20 mOhm -> +VSYS. +VSYS ali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
R71 : shunt de la jauge, prises Kelvin vers CSP/CSN
BQ25887 : ILIM 1.27k -> 1 A max en entree (reglable plus bas en I2C). CBSET 100 Ohm -> ~40 mA d equilibrage. TH1/TH2 : NTC sur la carte, a placer au plus pres des connecteurs de cellules. EP RGE a verifier vs datasheet.
R70 : shunt INA226 (feuille Mesures env.), prises Kelvin vers U41 IN+/IN-

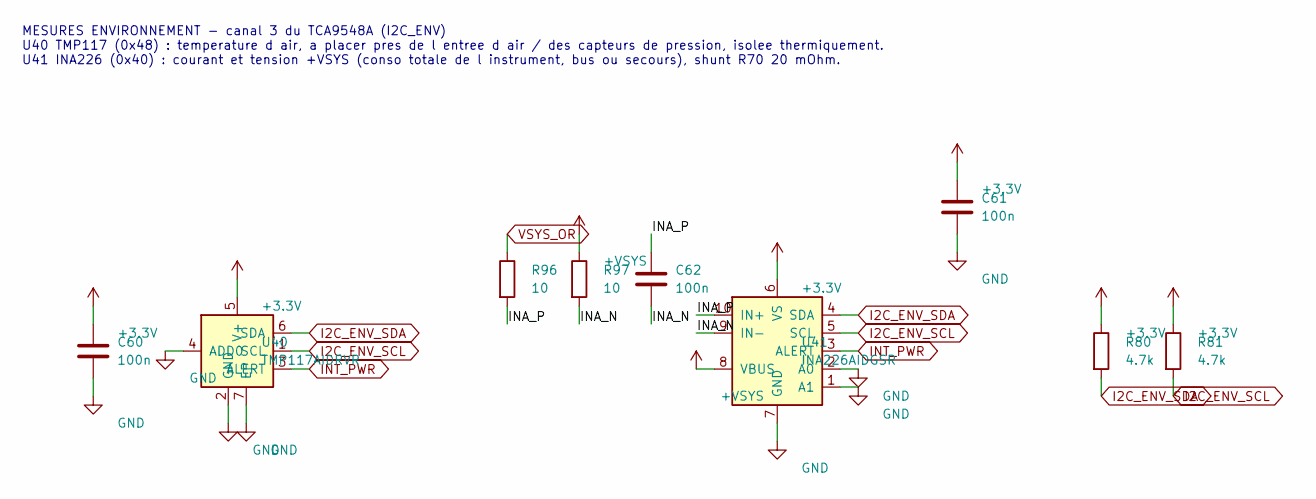
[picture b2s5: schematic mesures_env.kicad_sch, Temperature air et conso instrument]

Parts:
C60, C61, C62: 100n; C_0603_1608Metric
R80, R81: 4.7k; R_0603_1608Metric
R96, R97: 10; R_0603_1608Metric
U40: TMP117AIDRVR; WSON-6-1EP_2x2mm_P0.65mm_EP1x1.6mm
U41: INA226AIDGSR; MSOP-10_3x3mm_P0.5mm

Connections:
+3.3V: C60.1, C61.1, R80.1, R81.1, U40.5 (V+), U41.6 (VS); also elsewhere on the board
+VSYS: R97.1, U41.8 (VBUS); also elsewhere on the board
/Mesures env/INA_N: C62.2, R97.2, U41.9 (IN-)
/Mesures env/INA_P: C62.1, R96.2, U41.10 (IN+)
GND: C60.2, C61.2, U40.2 (GND), U40.4 (ADD0), U40.7 (EP), U41.1 (A1), U41.2 (A0), U41.7 (GND); also elsewhere on the board
I2C_ENV_SCL: R81.2, U40.1 (SCL), U41.5 (SCL); also elsewhere on the board
I2C_ENV_SDA: R80.2, U40.6 (SDA), U41.4 (SDA); also elsewhere on the board
INT_PWR: U40.3 (ALERT), U41.3 (ALERT); also elsewhere on the board
VSYS_OR: R96.1; also elsewhere on the board

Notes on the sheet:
MESURES ENVIRONNEMENT - canal 3 du TCA9548A (I2C_ENV) U40 TMP117 (0x48) : temperature d air, a placer pres de l entree d air / des capteurs de pression, isolee thermiquement. U41 INA226 (0x40) : courant et tension +VSYS (conso totale de l instrument, bus ou secours), shunt R70 20 mOhm.
